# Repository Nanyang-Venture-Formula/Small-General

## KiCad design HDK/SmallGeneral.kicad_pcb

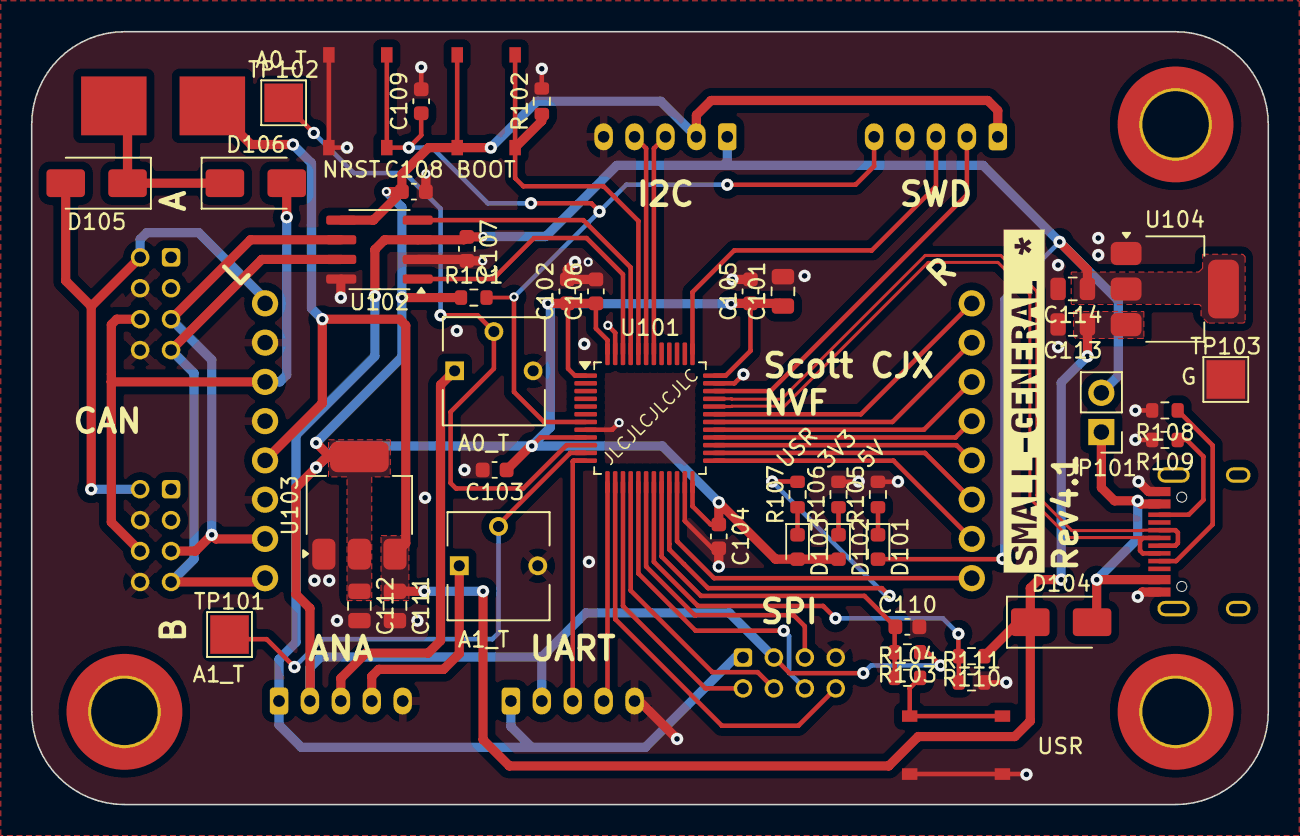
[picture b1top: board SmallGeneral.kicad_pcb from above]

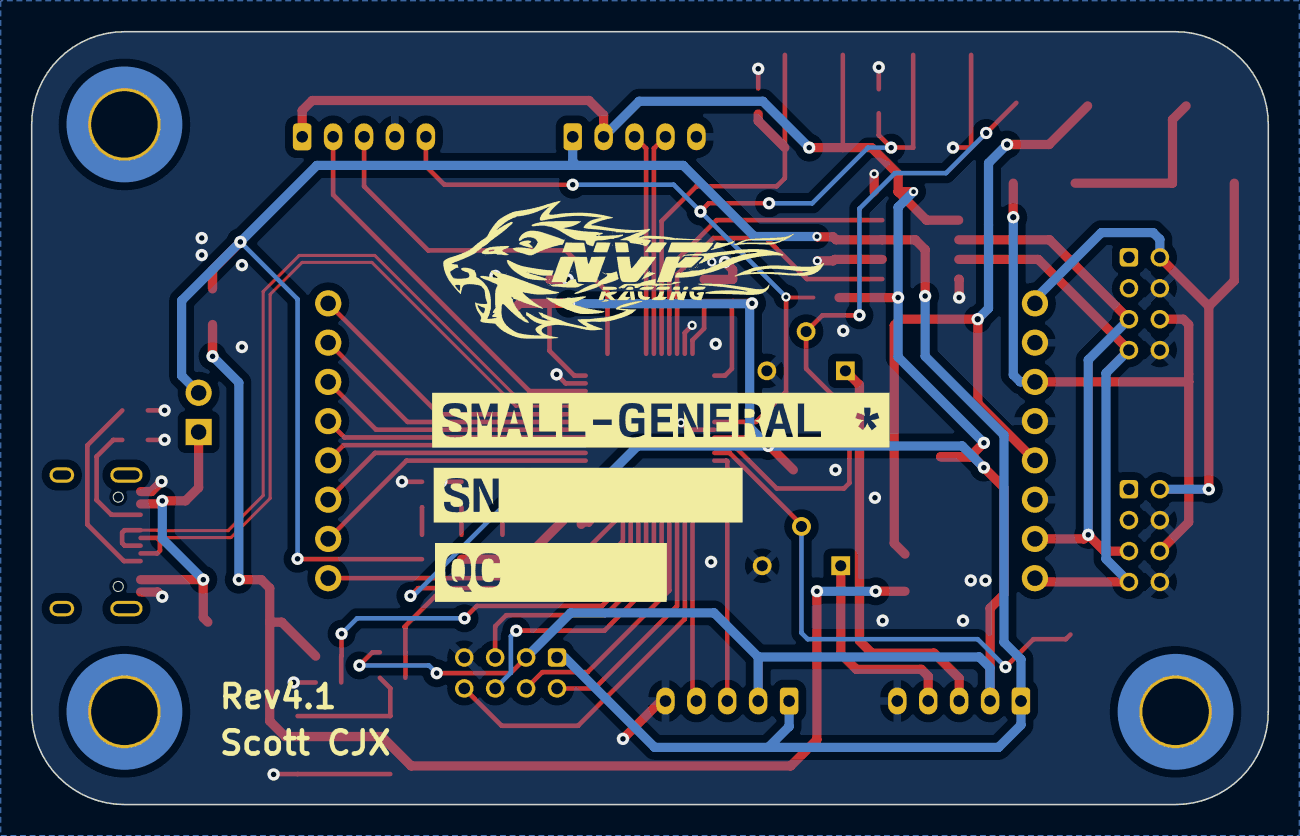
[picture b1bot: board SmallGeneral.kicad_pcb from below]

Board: 2 copper layers, 80.0 x 50.0 mm, 51 parts (3 on the bottom side), 48 nets.

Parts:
C101: 4u7; C_0805_2012Metric
C102, C103, C104, C105, C106, C107, C108, C109, C110: 100n; C_0603_1608Metric
C111, C112, C113, C114: 2u2; C_0805_2012Metric
D101: GREEN; LED_0603_1608Metric
D102: RED; LED_0603_1608Metric
D103: BLUE; LED_0603_1608Metric
D104, D105, D106: SS14; D_SMA
F101: Fuse; FUSE-Littelfuse_Nano2_154x
J101: USB_C; USBC_HRO_TYPE-C-31-M-12
JP101: Jumper_2_Open; PinHeader_1x02_P2.54mm_Vertical
R101, R102, R103, R110: 10k; R_0603_1608Metric
R104, R111: 1k; R_0603_1608Metric
R105, R106, R107: 300; R_0603_1608Metric
R108, R109: 5k1; R_0603_1608Metric
RV101, RV102: 10k; RV_Bourns_3362
SG101: Small-General Actual
SW101, SW102, SW103: SW_Push; PushBtn_TS-1187A-B-A-B
TP101, TP102, TP103: TestPoint; TestPoint_Pad_2.5x2.5mm
U101: STM32F072CBT6; LQFP-48_7x7mm_P0.5mm
U102: TJA1042T-3; SOIC-8_3.9x4.9mm_P1.27mm
U103: AMS1117-3.3; SOT-223-3_TabPin2
U104: AMS1117-5.0; SOT-223-3_TabPin2
kibuzzard-65C10821: G***; kibuzzard-65C10821
kibuzzard-65C10836: G***; kibuzzard-65C10836
kibuzzard-65CCCADD: G***; kibuzzard-65CCCADD
kibuzzard-65CCCB35: G***; kibuzzard-65CCCB35

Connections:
+3V3: C101.1, C102.1, C103.1, C104.1, C105.1, C106.1, C108.1, C112.1, D102.2 (A), D103.2 (A), R101.1, R103.1, SG101.C2 (3V3), SG101.D2 (3V3), SG101.E2 (3V3), SG101.F2 (3V3), SG101.G1 (3V3), SW101.2, U101.1 (VBAT), U101.9 (VDDA), U101.24 (VDD), U101.36 (VDDIO2), U101.48 (VDD), U102.5 (VIO), U103.2 (VO)
+5V: C107.1, C114.1, D101.2 (A), JP101.2 (B), SG101.C1 (5V), SG101.D1 (5V), SG101.E1 (5V), SG101.F1 (5V), U102.3 (VCC), U104.2 (VO)
/A0: RV101.1, SG101.C3 (A1)
/A0_MCU: RV101.2, TP102.1, U101.10 (PA0)
/A1: RV102.1, SG101.C4 (A0)
/A1_MCU: RV102.2, TP101.1, U101.11 (PA1)
/BOOT0: R102.1, SW101.1, U101.44 (BOOT0)
/CAN_H: SG101.A8 (CAN_H), SG101.B8 (CAN_H), SG101.L8 (CAN_H), U102.7 (CANH)
/CAN_L: SG101.A7 (CAN_L), SG101.B7 (CAN_L), SG101.L7 (CAN_L), U102.6 (CANL)
/CAN_RX: U101.45 (PB8), U102.4 (RXD)
/CAN_TX: U101.46 (PB9), U102.1 (TXD)
/CC1: J101.A5 (CC1), R108.1
/CC2: J101.B5 (CC2), R109.1
/I2C_SCL: SG101.F3 (I2C_SCL), U101.42 (PB6)
/I2C_SDA: SG101.F4 (I2C_SDA), U101.43 (PB7)
/NRST: C109.1, R101.2, SG101.G5 (NRST), SW102.1, U101.7 (NRST)
/PA8: SG101.R3 (PA8), U101.29 (PA8)
/PB11: SG101.R8 (PB11), U101.22 (PB11)
/PB12: SG101.R7 (PB12), U101.25 (PB12)
/PB13: SG101.R6 (PB13), U101.26 (PB13)
/PB14: SG101.R5 (PB14), U101.27 (PB14)
/PB15: SG101.R4 (PB15), U101.28 (PB15)
/SPI_CS: SG101.E8 (SPI_CS), U101.14 (PA4)
/SPI_IRQ: SG101.E3 (SPI_IRQ), U101.18 (PB0)
/SPI_MISO: SG101.E6 (SPI_MISO), U101.16 (PA6)
/SPI_MOSI: SG101.E7 (SPI_MOSI), U101.17 (PA7)
/SPI_SCLK: SG101.E5 (SPI_SCLK), U101.15 (PA5)
/SWCLK: SG101.G3 (SWCLK), U101.37 (PA14)
/SWDIO: SG101.G2 (SWDIO), U101.34 (PA13)
/UART2_RX: SG101.D4 (UART_RX), U101.13 (PA3)
/UART2_TX: SG101.D3 (UART_TX), U101.12 (PA2)
/UART_RX: SG101.R1 (PA10), U101.31 (PA10)
/UART_TX: SG101.R2 (PA9), U101.30 (PA9)
/USB_D+: J101.A6 (D+), J101.B6 (D+), U101.33 (PA12)
/USB_D-: J101.A7 (D-), J101.B7 (D-), U101.32 (PA11)
/USR_BTN: C110.1, R103.2, R104.1, U101.20 (PB2)
/USR_LED: R107.2, U101.21 (PB10)
/V_{SENSE}: R110.2, R111.1, U101.19 (PB1)
GND: C101.2, C102.2, C103.2, C104.2, C105.2, C106.2, C107.2, C108.2, C109.2, C110.2, C111.2, C112.2, C113.2, C114.2, J101.A1 (GND), J101.A12 (GND), J101.B1 (GND), J101.B12 (GND), R102.2, R105.2, R106.2, R108.2, R109.2, R111.2, RV101.3, RV102.3, SG101.A2 (GND), SG101.A4 (GND), SG101.B2 (GND), SG101.B4 (GND), SG101.C5 (GND), SG101.D5 (GND), SG101.E4 (GND), SG101.F5 (GND), SG101.G4 (GND), SG101.L2 (GND), SG101.L4 (GND), SG101.L6 (GND), SW102.2, SW103.2, TP103.1, U101.8 (VSSA), U101.23 (VSS), U101.35 (VSS), U101.47 (VSS), U102.2 (GND), U102.8 (STB), U103.1 (GND), U104.1 (GND)
unnamed: D101.1 (K), R105.1
unnamed: D102.1 (K), R106.1
unnamed: D103.1 (K), R107.1
unnamed: D105.1 (K), D106.1 (K), F101.1
unnamed: R104.2, SW103.1
V1: D105.2 (A), SG101.A1 (V1), SG101.B1 (V1), SG101.L1 (V1)
V2: D106.2 (A), SG101.A3 (V2), SG101.B3 (V2), SG101.L3 (V2)
VBUS: D104.2 (A), J101.A4 (VBUS), J101.A9 (VBUS), J101.B4 (VBUS), J101.B9 (VBUS), JP101.1 (A)
VCC: C111.1, C113.1, D104.1 (K), F101.2, R110.1, SG101.L5 (VCC), U103.3 (VI), U104.3 (VI)

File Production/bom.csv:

Designator,Footprint,Quantity,Value,LCSC Part #
C101,0805,1,4u7,C1779
"C102, C103, C104, C105, C106, C107, C108, C109, C110",0603,9,100n,C14663
"C111, C112, C113, C114",0805,4,2u2,C377773
D101,0603,1,GREEN,C434423
D102,0603,1,RED,C2286
D103,0603,1,BLUE,C965807
"D104, D105, D106",D_SMA,3,SS14,C2480
F101,FUSE-Littelfuse_Nano2_154x,1,Fuse,C206919
J101,USBC_HRO_TYPE-C-31-M-12,1,USB_C,C165948
JP101,PinHeader_1x02_P2.54mm_Vertical,1,Jumper_2_Open,-
"R101, R102, R103, R110",0603,4,10k,C25804
"R104, R111",0603,2,1k, C21190
"R105, R106, R107",0603,3,300,C23025
"R108, R109",0603,2,5k1,C23186
"RV101, RV102",RV_Bourns_3362,2,10k,C58159
SG101,Small-General Actual,1,~,-
"SW101, SW102, SW103",PushBtn_TS-1187A-B-A-B,3,SW_Push,C318884
"TP101, TP102, TP103",TestPoint_Pad_2.5x2.5mm,3,TestPoint,-
U101,LQFP-48_7x7mm_P0.5mm,1,STM32F072CBT6,C81720
U102,SOIC-8_3.9x4.9mm_P1.27mm,1,TJA1042T-3,C132227
U103,SOT-223-3_TabPin2,1,AMS1117-3.3,C6186
U104,SOT-223-3_TabPin2,1,AMS1117-5.0,C6187

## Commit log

2024-02-05 Initialize gh-pages
2024-02-05 Moving files docs/* LICENSE using main
2024-02-05 Deploying to gh-pages from @ Nanyang-Venture-Formula/Small-General@b5e813e713e885ee3e17b0bf8f7ca736155ffc8d 🚀
2024-02-05 added rev1
2024-02-05 Deploying to gh-pages from @ Nanyang-Venture-Formula/Small-General@dbec67e0bc32b61fd3eaf2f058449da4c20f9528 🚀
2024-02-14 updated rev3
2024-02-14 updated Trim Pot Switch
2024-02-14 fixed rev3 switch
2024-02-14 Deploying to gh-pages from @ Nanyang-Venture-Formula/Small-General@db51c207b7705968e12671ab1df1e52fde54d375 🚀
2024-03-17 updated docs
2024-03-17 Deploying to gh-pages from @ Nanyang-Venture-Formula/Small-General@6743138d68fdce8216f7951eec0163138f330556 🚀
2024-03-18 added docs
2024-03-18 Deploying to gh-pages from @ Nanyang-Venture-Formula/Small-General@c8727ade2bde58ef70672274132b3488cdedc8eb 🚀
2024-04-08 updated rev4
2024-04-08 Deploying to gh-pages from @ Nanyang-Venture-Formula/Small-General@7e0682e76d8d31db93e2a0044be0bf48fe7c0c05 🚀
2024-04-08 updated rev4.1
2024-04-08 updated docs
2024-04-08 added prod and ibom
2024-04-08 updated schematics
2024-04-08 fixed schematics
2024-04-08 disabled actions
2024-04-09 fixed docs
2024-04-09 updated correct gerbers
